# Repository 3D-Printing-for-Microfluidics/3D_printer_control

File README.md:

# 3D Printer Control System

A sophisticated control system for custom DLP-SLA 3D printers, built with Flask and WebSocket communication. This system provides a robust web interface for controlling and monitoring 3D printing operations, with support for various hardware configurations and real-time feedback.

# Overview

This system is designed to control custom DLP-SLA 3D printers using a JSON-based print file format. The print files are validated using a custom JSON schema validator to ensure proper formatting and compatibility. The system supports multiple printer configurations and can be adapted to different hardware setups through its modular architecture.

## System Architecture

### Backend
- Built on Flask web server with modular blueprint structure
- Uses Socket.IO for real-time bidirectional communication between frontend and backend
- Implements a modular hardware driver system for various printer components
- Database-driven job queue management using SQLAlchemy
- Comprehensive logging system with configurable levels and file rotation
- Error handling and recovery mechanisms for hardware failures

### Frontend
- JINJA2 templating engine for HTML structure
- Bootstrap (Darkly theme) for responsive styling
- JavaScript libraries:
  - Socket.IO for real-time communication
  - AJAX for asynchronous requests
  - jQuery for DOM manipulation
  - Popper.js for tooltips and popovers
- Dynamic UI updates for real-time printer status
- Responsive design for various screen sizes

## Hardware Configuration

The system uses a flexible hardware configuration system that:
- Loads hardware configurations based on device hostname
- Supports multiple types of hardware drivers:
  - Virtual hardware (screen, coord_systems, external_control)
  - Abstract base classes and generic drivers (e.g., Visitech light engine, ACS XY/BP stage, Hexapod TTR/focus stage)
  - Regular hardware drivers
- Includes firmware management capabilities through `flash_firmware.sh` RPi script
- Provides dummy drivers for testing and development
- Supports hardware-specific calibration and configuration
- Implements hardware abstraction layers for consistent control interfaces

### Hardware Types
1. **Motion Control**
   - XY stages (ACS, custom implementations)
   - Z-axis control
   - Build plate control
   - Tip-tilt-rotate (TTR) stages
   - Focus stages

2. **Light Control**
   - DLP light engines
   - Screen control systems

3. **Sensors**
   - Load cells
   - Keyence sensors
   - Environmental sensors
   - Accelerometers
   - Light measurement systems

4. **Auxiliary Systems**
   - Vacuum control
   - GPIO control
   - Film control
   - Environmental monitoring

## Core Components

### Manual Controls
- Each hardware driver has associated frontend controls
- Automatically populated based on hardware configuration
- Provides fine-grained control over hardware components
- Allows modification of system settings
- Real-time feedback and status updates
- Safety interlocks and emergency stop functionality

### Views
1. **Print History**
   - Displays recent prints with detailed information
   - Enables job download and re-queue functionality
   - Print success/failure statistics
   - Job parameter history

2. **Server Logs**
   - Shows last 2 weeks of logs
   - Includes calibration position logs
   - Hardware-specific diagnostic information
   - Error tracking and debugging tools

3. **Calibration**
   - Manages printer calibration settings
   - Supports focus, tip, tilt adjustments
   - Integrates with Keyence sensors and Hexapod systems
   - Calibration profile management
   - Automated calibration routines

### Main Printer Control (home.py)
The central control system that:
- Manages print uploads and job queue
- Handles printer planarization
- Controls print operations (start/pause/resume/stop)
- Provides real-time feedback (loadcell data, log messages)
- Implements a dynamic class hierarchy for hardware control
- Error handling and recovery
- State management and synchronization

## Hardware Control Architecture

The system uses a dynamic class composition approach:
- Base `print_control` class defines core functionality
- Hardware-specific subclasses extend functionality
- Class composition is determined by hardware configuration
- Import order is critical for proper initialization and print operations
- Thread-safe operation handling
- Event-driven architecture for hardware interactions

# Raspberry Pi Deployment

This section details the setup process for deploying the system on a Raspberry Pi 5 with NVME storage. See also the `How to do a full install of a HR5 Raspberry Pi` ProjectWiki page for a more detailed guide with rationale.

### Hardware Requirements

- Raspberry Pi 5
- Pimoroni NVME base
- Crucial P3 Plus 1TB SSD (or compatible)
- External SSD housing (for initial setup)

### Initial Setup

1. **Physical Setup**
   - Install NVME SSD and Pimoroni NVME base
   - Follow [Pimoroni NVME base tutorial](https://learn.pimoroni.com/article/getting-started-with-nvme-base)

2. **OS Installation**
   - Download Raspberry Pi Imager
   - Flash Raspberry Pi OS (64-bit) 2024-03-15
   - Configure initial settings:
     - Set hostname (e.g., HR5, MR1v1, HR3v3)
     - Username: pi
     - Password: 3dprinter
     - Timezone: Denver
     - Enable SSH

3. **System Configuration**
   - Configure SSD boot:
     ```bash
     # Edit /boot/firmware/config.txt
     dtparam=pciex1
     nvme_core.default_ps_max_latency_us=0 pcie_aspm=off
     
     # Configure EEPROM
     sudo rpi-eeprom-config --edit
     # Set:
     BOOT_ORDER=0xf416
     PCIE_PROBE=1
     ```
   - Set system clock: `date -s 'YYYY-MM-DD HH:MM:SS'`
   - Configure network:
     - Connect to BYU-Wifi via https://onboard.byu.edu/guest/public/index.html
     - Set static ethernet address (192.168.0.1/24) using `sudo nmtui`
   - Switch to legacy X11:
     ```bash
     sudo raspi-config
     # Advanced Options -> Wayland -> X11
     ```
   - Disable screen blanking:
     ```bash
     sudo raspi-config
     # Display Options -> Screen Blanking -> No
     ```

4. **USB Device Configuration**
   - Create udev rules for USB devices:
     ```bash
     # Wintech
     sudo nano /etc/udev/rules.d/99-wintech.rules
     SUBSYSTEM=="usb",ATTRS{idVendor}=="0451",ATTRS{idProduct}=="c900",GROUP="users",MODE:="0666"
     
     # MKS Controller
     sudo nano /etc/udev/rules.d/99-mks.rules
     SUBSYSTEM=="usb",ATTRS{idVendor}=="0403",ATTRS{idProduct}=="6001",GROUP="users",MODE:="0666"
     
     # Thorlabs Power Meter
     sudo nano /etc/udev/rules.d/99-thorlabspm100.rules
     SUBSYSTEM=="usb",ATTRS{idVendor}=="1313",ATTRS{idProduct}=="8072",GROUP="users",MODE:="0666"
     ```
   - Reload udev rules: `sudo udevadm control --reload-rules`

5. **System Logging**
   - Configure journald:
     ```bash
     # Edit /etc/systemd/journald.conf
     [Journal]
     MaxRetentionSec=1week
     MaxFileSec=1day
     
     # Create journal directory
     mkdir /var/log/journal
     sudo systemd-tmpfiles --create --prefix /var/log/journal
     ```

### Software Installation

1. **Clone Repositories**
   ```bash
   git clone https://github.com/3D-Printing-for-Microfluidics/IP_address_service.git
   git clone https://github.com/gregnordin/3D_printer_control.git
   ```

2. **Install IP Address Service**
   ```bash
   cd IP_address_service/ip_address_service
   sudo -s source ip_address_service_setup.sh
   ```

3. **Setup Python Environment**
   ```bash
   cd 3D_printer_control
   python -m venv env
   source env/bin/activate
   mkdir logs
   
   # Upgrade pip and setuptools
   pip install pip --upgrade
   pip install setuptools --upgrade
   ```

4. **Install Galil Driver**
   ```bash
   # Install CGLib Software
   sudo apt install ./requirements/galil-release_1_all.deb
   sudo apt update
   sudo apt install gclib gcapsd
   ```

5. **Install Python Dependencies**
   ```bash
   pip install -r requirements/prod.txt  # For production
   # or
   pip install -r requirements/dev.txt   # For development
   ```

   Key dependencies include:
   - Flask 3.0.3 with Flask-SocketIO 5.3.6 for web server and real-time communication
   - SQLAlchemy 2.0.31 and Flask-SQLAlchemy 3.1.1 for database management
   - Hardware control libraries:
     - gclib for Galil motion controllers
     - gpiod 2.2.0 and gpiozero 2.0.1 for GPIO control
     - pyserial 3.5 for serial communication
     - pyusb 1.2.1 for USB device control
   - Scientific computing:
     - numpy 2.0.0 and scipy 1.14.1 for numerical operations
     - matplotlib 3.10.1 for plotting
     - pandas 2.2.3 for data manipulation
   - Hardware-specific:
     - ThorlabsPM100 1.2.2 for power meter control
     - seabreeze 2.9.2 for spectrometer integration
     - PIPython 2.10.2.1 for PI motion controllers
   - System utilities:
     - psutil 6.0.0 for system monitoring
     - zeroconf 0.132.2 for network discovery
   - Development tools:
     - jsonschema 4.22.0 for JSON validation
     - scapy 2.5.0 for network analysis

6. **Setup Flask Database**
   ```bash
   source rpi/flask_db_setup.sh
   ```

7. **Configure Systemd Service**
   ```bash
   # Allow X server access
   export DISPLAY=:0.0
   xhost si:localuser:pi
   
   # Create service file
   sudo nano /etc/systemd/system/3d-printer-server.service
   ```
   Add to service file:
   ```ini
   [Unit]
   Description=3D Printer Server
   After=network.target
   
   [Service]
   Type=simple
   WorkingDirectory=/home/pi/3D_printer_control
   Environment=FLASK_APP=/home/pi/3D_printer_control/autoapp.py
   Environment=XAUTHORITY=/home/pi/.Xauthority
   Environment=DISPLAY=:0.0
   ExecStart=/home/pi/3D_printer_control/env/bin/python /home/pi/3D_printer_control/autoapp.py
   Restart=always
   
   [Install]
   WantedBy=multi-user.target
   ```
   Enable and start service:
   ```bash
   sudo systemctl daemon-reload
   sudo systemctl enable 3d-printer-server.service
   sudo systemctl start 3d-printer-server.service
   ```

### Display Configuration

1. **Setup Custom Resolutions**
   ```bash
   # Create autostart directory
   mkdir -p ~/.config/autostart
   
   # Create desktop entry
   nano ~/.config/autostart/xrandr.desktop
   ```
   Add to desktop entry:
   ```ini
   [Desktop Entry]
   Type=Application
   Exec=/home/pi/.config/autostart/xrandr.sh
   Hidden=false
   NoDisplay=false
   X-GNOME-Autostart-enabled=true
   Name[en_US]=Xrandr
   Name=Xrandr
   Comment[en_US]=Set custom resolution using xrandr
   Comment=Set custom resolution using xrandr
   ```
   
   Create resolution script:
   ```bash
   nano ~/.config/autostart/xrandr.sh
   ```
   Add to script:
   ```bash
   #!/bin/sh
   export DISPLAY=:0.0
   
   # Visitech resolution (2560x1600)
   xrandr --newmode "2560x1600_30" 132.68 2560 2608 2640 2720 1600 1603 1609 1623 +hsync -vsync
   xrandr --addmode HDMI-1 2560x1600_30
   xrandr --output HDMI-1 --mode 2560x1600_30
   
   # Wintech resolution (1920x1080)
   xrandr --newmode "1920x1080_60" 148.50 1920 2008 2096 2200 1080 1084 1089 1125 +hsync -vsync
   xrandr --addmode HDMI-2 1920x1080_60
   xrandr --output HDMI-2 --mode 1920x1080_60
   ```
   Make script executable:
   ```bash
   chmod +x ~/.config/autostart/xrandr.sh
   ```

### Additional Hardware Notes

- Spectrometer: Update firmware to NI-VISA version using Thorlabs Driver Switcher
- PI Hexapod stage: Update IP address to match subnet (192.168.x.x)
- ACS stages: Configure static IP and update to match subnet

# Development Setup

### Prerequisites
- Python 3.5 or higher
- Virtual environment (recommended)
- Required Python packages (see requirements/dev.txt)
- Git

### Installation Steps
1. Clone the repository
2. Create and activate virtual environment:
   ```bash
   python -m virtualenv env
   source env/bin/activate  # On Windows: env\Scripts\activate
   ```
3. Install dependencies:
   ```bash
   pip install -r requirements/dev.txt
   ```
4. Set up environment variables:
   ```bash
   export FLASK_APP=tests/dummy_server.py
   export FLASK_DEBUG=1  # For development mode
   ```
5. Initialize database:
   ```bash
   flask db init
   flask db migrate
   flask db upgrade
   ```

### Running the Development Server
1. Start the server:
   ```bash
   python $FLASK_APP
   ```
2. Access the web interface at `http://127.0.0.1:5000`
3. For external access, modify `app.py` to use `0.0.0.0:port`

### Development Tips
- Use Incognito mode to prevent browser caching
- Press `Ctrl+F5` in Chrome to force refresh
- Monitor terminal output for debug information
- Check logs in `printer_server/logs/`

# Active Branches

This repository maintains several branches for different printer configurations:
- `master` - Stable branch for 3D printers
- `dev/ branches` - Current active development branches
- `feature/ branches` - Branches adding new feature to 3D printers
- `stable/ branches` - Legacy release branches no longer in use
- `gen1-1` - Legacy software for HR1.1 3D printer

# Troubleshooting

### Common Issues

1. **Hardware Connection**
   - Check USB connections
   - Verify permissions
   - Test hardware directly
   - Check logs for errors

2. **Firmware Issues**
   - Verify firmware version
   - Check flash process
   - Review error logs
   - Test with dummy firmware

3. **Web Interface**
   - Clear browser cache
   - Check Socket.IO connection
   - Verify JavaScript console
   - Test in incognito mode

# Additional Resources

- [Flask Documentation](http://flask.pocoo.org/docs/1.0/quickstart/)
- [Python Virtual Environment Guide](https://docs.python.org/3/tutorial/venv.html)
- [Socket.IO Documentation](https://socket.io/docs/)
- [Bootstrap Documentation](https://getbootstrap.com/docs/)

# License

This project is licensed under the terms specified in the LICENSE.txt file.

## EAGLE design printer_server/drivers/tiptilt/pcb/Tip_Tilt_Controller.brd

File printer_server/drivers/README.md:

# 3D Printer Hardware Drivers

This directory contains the hardware drivers for controlling various components of the 3D printer system. The drivers are designed with a modular architecture that supports both real hardware and dummy implementations for testing.

## Driver Architecture

The driver system follows a hierarchical design with:
- Abstract base classes in `generic_drivers/` defining common interfaces
- Concrete implementations for specific hardware
- Dummy implementations for testing and development

### Base Classes

The `generic_drivers/` directory contains abstract base classes for different types of hardware:

1. **Stage Drivers**
   - `BPStageDriver`: Build platform stage control
   - `XYStageDriver`: XY motion stage control
   - `FocusStageDriver`: Focus stage control
   - `TTRStageDriver`: Tip-tilt-rotate stage control

2. **Communication Drivers**
   - `EthernetSerial`: Base class for Ethernet-based serial communication
   - `USBSerial`: Base class USB-based serial communication

## Available Drivers

### Motion Control
- `acs/`: ACS motion controller driver
- `galil/`: Galil motion controller driver
- `hexapod/`: Hexapod stage driver
- `thorlabs_apt`: Thorlabs motor driver for KDC101 and LTS stages
- `tiptilt/`: Custom Tip-tilt stage driver for optical alignment

### Light Control
- `screen/`: Screen control system
- `visitech/`: Visitech light engine driver
- `wintech/`: Wintech DLP controller driver

### Sensors
- `accelerometer/`: Accelerometer driver
- `environmental_sensors/`: Environmental monitoring sensors
- `keyence/`: Keyence confocal displacement sensor driver
- `loadcell/`: Load cell sensor for force measurement
- `photodiode/`: Photodiode sensor driver
- `spectrometer/`: Spectrometer driver

### Auxillary Control
- `external_control/`: External control system interface
- `gpio/`: General Purpose I/O control
- `mks/`: MKS 946 pressure controller driver
- `mks_teensy/`: Teensy-based MKS controller and GPIO interface

### Other
- `coord_systems/`: Coordinate system transformation utilities

## Driver Implementation

Each driver follows a common pattern:
1. Inherits from appropriate base class
2. Implements required interface methods
3. Provides hardware-specific functionality
4. Includes error handling and logging
5. Supports both real and dummy implementations

### Example Usage

```python
from printer_server.drivers.galil import Galil, Galil_dummy

# For real hardware
driver = Galil(config_dict=config, log_level=logging.INFO)

# For testing/development
driver = Galil_dummy(config_dict=config, log_level=logging.INFO)
```

## Adding New Drivers

To add a new driver:

1. Create a new directory in `drivers/`
2. Implement the driver class inheriting from appropriate base class
3. Create a dummy implementation for testing
4. Add driver configuration to hardware configuration JSON
5. Update `hardware_configuration.py` to support the new driver

## Testing

Each driver should have:
- A dummy implementation for testing
- Appropriate Manual Control _snip code

## Configuration

Drivers are configured through JSON files in the `hardware_configuration/` directory. Each driver can specify:
- Connection parameters
- Hardware-specific settings
- Dummy mode for testing
- Logging configuration

## Error Handling

Drivers implement comprehensive error handling:
- Connection failures
- Hardware communication errors
- Invalid commands
- Timeout handling
- Recovery procedures

## Logging

All drivers use the Python logging system with:
- Configurable log levels
- Hardware-specific log messages
- Error tracking
- Performance monitoring

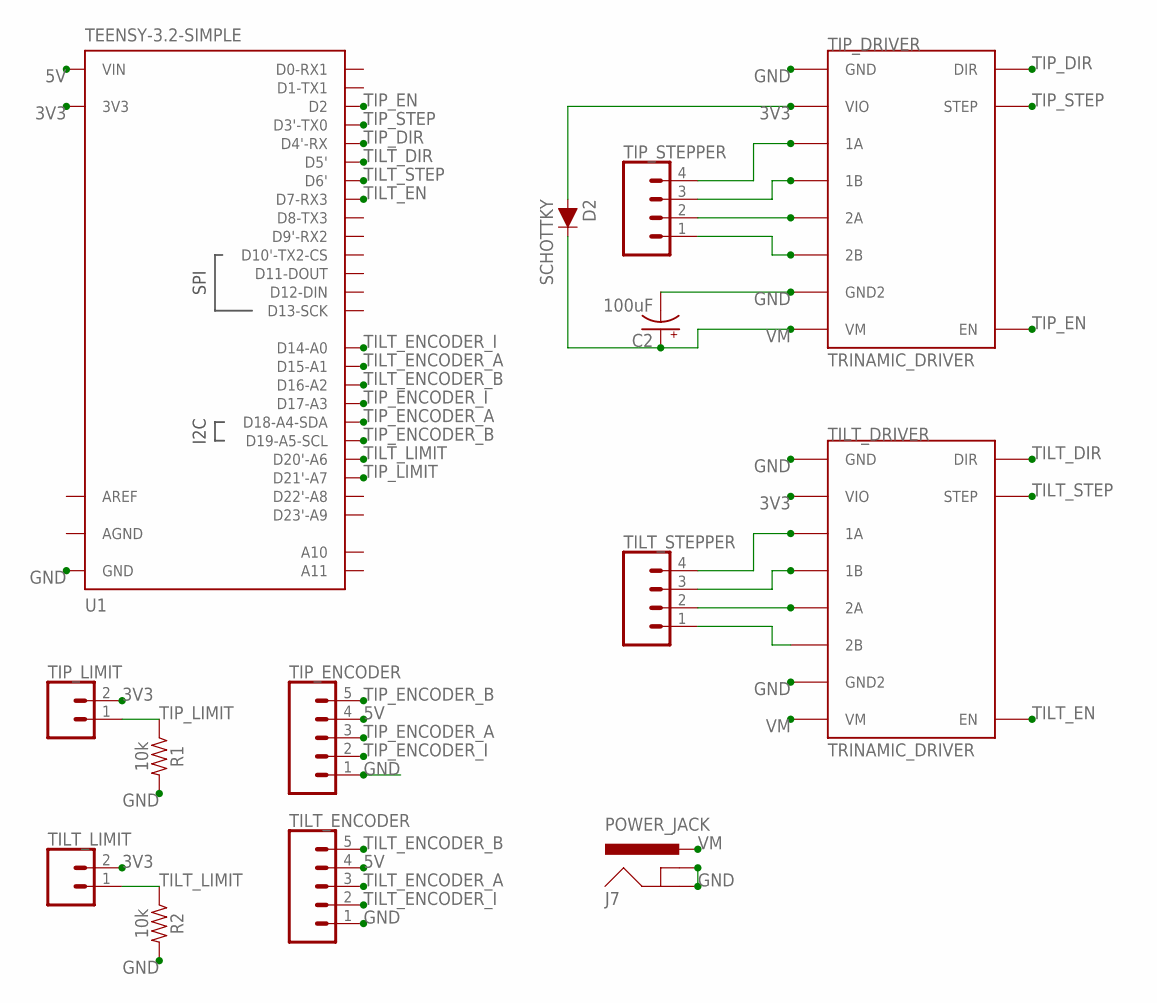
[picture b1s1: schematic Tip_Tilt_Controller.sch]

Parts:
C2: 100uF; CPOL-RADIAL-2.5MM-6.5MM
D2: SCHOTTKY; DIODE-1N4148
J7: POWER_JACK; POWER_JACK_PTH
R1, R2: 10k; AXIAL-0.3
TILT_DRIVER: TRINAMIC_DRIVER
TILT_ENCODER: CONN_05; 1X05
TILT_LIMIT: CONN_02; 1X02
TILT_STEPPER: CONN_04PTH; 1X04
TIP_DRIVER: TRINAMIC_DRIVER
TIP_ENCODER: CONN_05; 1X05
TIP_LIMIT: CONN_02; 1X02
TIP_STEPPER: CONN_04PTH; 1X04
U1: TEENSY-3.2-SIMPLE

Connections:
3V3: D2.A, TILT_DRIVER.5V (VIO), TILT_LIMIT.2, TIP_DRIVER.5V (VIO), TIP_LIMIT.2, U1.3.3V (3V3)
5V: TILT_ENCODER.4, TIP_ENCODER.4, U1.VIN
AGND: U1.AGND
AREF: U1.AREF
GND: C2.2 (-), J7.GND, J7.GNDBREAK, R1.P$2 (2), R2.P$2 (2), TILT_DRIVER.GND, TILT_DRIVER.GND2, TILT_ENCODER.1, TIP_DRIVER.GND, TIP_DRIVER.GND2, TIP_ENCODER.1, U1.GND
unnamed: TIP_DRIVER.1A, TIP_STEPPER.4
unnamed: TIP_DRIVER.1B, TIP_STEPPER.3
unnamed: TIP_DRIVER.2A, TIP_STEPPER.2
unnamed: TIP_DRIVER.2B, TIP_STEPPER.1
unnamed: TILT_DRIVER.1A, TILT_STEPPER.4
unnamed: TILT_DRIVER.1B, TILT_STEPPER.3
unnamed: TILT_DRIVER.2A, TILT_STEPPER.2
unnamed: TILT_DRIVER.2B, TILT_STEPPER.1
TILT_DIR: TILT_DRIVER.DIR, U1.5 (D5')
TILT_EN: TILT_DRIVER.EN, U1.7 (D7-RX3)
TILT_ENCODER_A: TILT_ENCODER.3, U1.15 (D15-A1)
TILT_ENCODER_B: TILT_ENCODER.5, U1.16 (D16-A2)
TILT_ENCODER_I: TILT_ENCODER.2, U1.14 (D14-A0)
TILT_LIMIT: R2.P$1 (1), TILT_LIMIT.1, U1.20 (D20'-A6)
TILT_STEP: TILT_DRIVER.STEP, U1.6 (D6')
TIP_DIR: TIP_DRIVER.DIR, U1.4 (D4'-RX)
TIP_EN: TIP_DRIVER.EN, U1.2 (D2)
TIP_ENCODER_A: TIP_ENCODER.3, U1.18 (D18-A4-SDA)
TIP_ENCODER_B: TIP_ENCODER.5, U1.19 (D19-A5-SCL)
TIP_ENCODER_I: TIP_ENCODER.2, U1.17 (D17-A3)
TIP_LIMIT: R1.P$1 (1), TIP_LIMIT.1, U1.21 (D21'-A7)
TIP_STEP: TIP_DRIVER.STEP, U1.3 (D3'-TX0)
VM: C2.1 (+), D2.C, J7.PWR, TILT_DRIVER.VM, TIP_DRIVER.VM

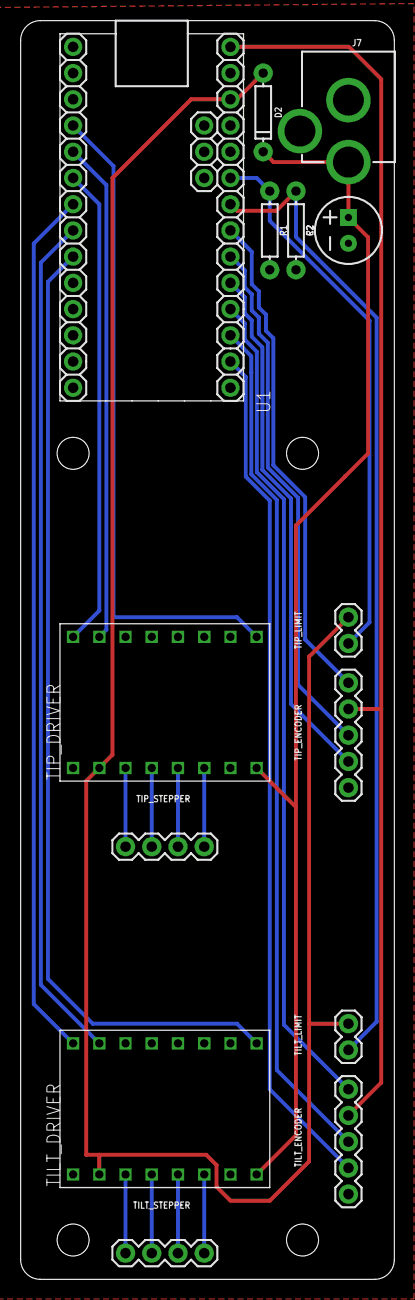
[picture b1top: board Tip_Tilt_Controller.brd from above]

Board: 2 copper layers, 36.2 x 121.9 mm, 14 parts (0 on the bottom side), 26 nets.

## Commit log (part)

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2024-12-31 Prevent loop racing in TT
2024-12-31 Actually call TTR logging start/stop
2024-12-31 Fix other race events
2024-12-31 speed up keyence measurements
2024-12-31 Remove extra wait in light engine driver exposures
2024-12-31 Increase resolution and update rate of loadcell plot
2024-12-31 Fix bug in GPIO film mc
2024-12-31 Rename tt log
2025-01-02 Fixed Tiptilt driver float rounding
2025-01-02 Change last commit to increse precision
2025-01-02 One more...
2025-01-02 Fix cast error in KDC
2025-01-03 Fix ttr bug in calibration
2025-01-03 Fix trig error in MirrorTipTilt
2025-01-03 Add undef if tt not initialized. Speed up movements
2025-01-03 Add nm label to le source
2025-01-09 Add microcode libraries, firmware scripts, and firmware binaries
2025-01-09 Split mks and mks_teensy, also a few bug fixes
2025-01-09 Fix bug introduced in f4f2584
2025-01-31 Reduce loadcell drawing
2025-01-31 Hopefully fix TT loop failing
2025-01-31 Reduce loadcell planarization to 35N
2025-01-31 Update HR5 settings (note grayscale corr is included...)
2025-01-31 Add grayscale corrections
2025-01-31 Add TestControl
2025-01-31 Update light_measurement_control
2025-01-31 Add second finish plan for HR5
2025-02-24 Add more delay to degas vent
2025-02-24 First pass at test code for hannah and heidi
2025-02-24 Fix bug in last
2025-02-24 Add multiple scan lines to test
2025-03-07 Add vaccum control for prints (still need to do some kind of json enabling)
2025-03-07 Add logging to last commit
2025-03-07 Adjusting vacuum targets
2025-03-07 Add extra check ot bell jar venting
2025-03-07 Move MKSControl before LoadcellControl
2025-03-07 Fix critical bug
2025-03-07 Fix bug in vaccum control
2025-03-10 Add "Print under vacuum" to json and add planarization vacuum logging
2025-03-10 Cleanup loadcell set_log_file
2025-03-10 Only do planarization a 2nd time if "Print under vacuum"
2025-03-10 Fix bug in new vaccum code
2025-03-10 Another fix to vacuum code
2025-03-13 Add Y-offset to keyence line test
2025-03-17 Hopefully fix accelerometer freezing
2025-03-19 Fix issue with vacuum valve priorities
2025-03-21 Still trying to fix hanging at end of print
2025-03-25 Worked on grayscale scan and analysis test code
2025-03-25 Speed up print and add correction
2025-03-25 Fix bug in last commit
2025-03-28 Change fast photodiode position
2025-03-28 Tweek last commit
2025-04-09 Add film membrane to json and validator
2025-04-09 Recompress cleaned uploaded file
2025-04-11 Update requirements again
2025-04-11 Updated installation README and files to save galil/gclib install files
2025-04-11 Updated reqirements to include gclib
2025-04-14 Add normaization factor of 1 to 3v3u json
2025-04-14 Fix bug in normalization base case
2025-04-15 Fix bug in MR1v1 calibration
2025-04-19 Add thermal drift calculations for MR1v1
2025-04-19 Fix bugs in new keyence thermal code
2025-04-19 Fix bug in grayscale on visitech
2025-04-19 Fix another bug in the thermal code
2025-04-19 Tweek progress bar
2025-04-19 Add debug statements to new keyence measurements
2025-04-19 Trying to figure out what is not working
2025-04-20 Switch temporary print statements to event log
2025-04-21 Clean up code, add origin thermal measure, and fix crash
2025-04-21 Correct for backlash in griffin focus & add thermal expantion log
2025-04-21 Fix bug in thermal logging
2025-04-21 Another bug
2025-04-21 Remove keyence focus stage jiggle
2025-04-21 Final cleanup
2025-04-22 Remove temp logging, move all keyence logs to log file, swap origin measurement to only failed cont measurements
2025-04-22 Fix bug
2025-04-22 Update again
2025-04-22 Again
2025-04-23 Fix typo
2025-05-09 Add wintech fan control
2025-05-09 More bug fix
2025-05-09 Set fans to be default on
2025-05-09 Swap fan polarity
2025-05-09 Undo last
2025-05-09 Final fan commit
2025-07-28 Fix bug in dev.txt
2025-07-28 Update 3v3u loadcell settings
2025-07-29 update to galil controller
2025-07-30 Update KDC and os1 hardware config
2025-07-30 Fixed os1v0 hw-conf and renamed kdc101
2025-07-30 Fix os1 loadcell pid
2025-07-30 Fix hw-conf
2025-07-30 Fix multi-inheritance of thorlabs-apt driver
2025-07-31 Fix apt limits bug
2025-07-31 Add delay after apt home
2025-07-31 Update ttrf limits to use rad
2025-07-31 Update os1 coords, speeds, limits, and homing speeds
2025-07-31 Update 3 series to use kdc101_ttrf
2025-08-01 Fix apt connect
2025-08-01 Fix apt limit issues
2025-08-01 Update apt homing speeds
2025-08-01 Tweek log messages
2025-08-01 Cleanup apt
2025-08-01 Fix limits
2025-08-01 Fix bug in ttrf limits
2025-08-01 Update bp, xy, focus limits to update on mc
2025-08-01 Double tip/tilt angles
2025-08-05 updated serial number
2025-08-05 planarization motor initialization bugfixes
2025-08-05 planarization motor initialization bug fixes
2025-08-05 bug fixes
2025-08-05 updated planarization firmware
2025-08-05 firmware flashing bug fixed?
2025-08-05 turned on dummy drivers for testing
2025-08-05 firmware flashing name reconcilliation
2025-08-06 small bug squash
2025-08-06 Update OS1 hwconf
2025-08-06 Fix bugs in motor planarization
2025-08-06 fixed pointer issue
2025-08-06 Fix bug in planarization threading
2025-08-07 Mostly finish motorized planarization
2025-08-07 added supported versions
2025-08-07 Fix bug in ttr join
2025-08-07 Fix bug in clickable row
2025-08-08 Add first pass at keyence tip/tilt
2025-08-12 separation of photodiode and spectrometer in light measurement control
2025-08-12 Add in Visitech initialization check
2025-08-12 manual controls for planarization motor
2025-08-12 intuitive change so that loosen sets target torque to 0.0
2025-09-05 Add orientation to config json
2025-09-05 Update OS1 coords
2025-09-05 Adjust OS1 speeds and accelerations
2025-09-05 Adjust OS1 planarization settings
2025-09-05 Try to fix rare screen drawing failure
2025-09-05 Tweek kdc101ttrf tip multiplier
2025-09-05 Adjust visitech DMD operation to wait until video lock
2025-09-05 Force visitech to validate video lock on init
2025-09-05 Add 999 schema to OS1
2025-09-05 Swap auto_tip_tilt to test control
2025-09-05 Overhaul test control (progress, le alignment, stage linking, new photodiode centering process, grayscale json updating, keyence/photodiode tip/tilt) BROKEN HR5 MIRRORING
2025-09-05 Fix bugs in and tweek planarization
2025-09-18 Fix bug in MR1 Visitech focus
2025-10-15 Add variables to print schema
2025-10-15 Add simpleeval req
2025-10-15 Fix last
2025-10-16 Update HR5 coords, vacuum levels, and grayscale correction code
2025-10-16 Add logging to screen image not found
2025-10-16 Add calibration images to visitech
2025-10-16 Remove print statement
2025-10-16 Add grayscale correction image to OS1 hwconf
2025-10-16 Rename keyence control
2025-10-16 Update test_control plotting and use builtin calibration images
2025-10-16 Update gitignore
2025-11-19 Update MR1v1 coords
2025-11-19 Update json validator with membrane on film change
2026-01-29 debugging on printer pi
2026-02-09 Updated to json v5
2026-02-09 Fix schema bug
2026-02-09 Take 2
2026-02-09 Take 3
2026-02-09 Ok. For reals this time??
2026-02-10 Fix bug in squeeze force and add debug print for testing
2026-02-10 Remove debug prints
2026-02-10 Fixed last
2026-02-10 Fix printer_compatibiliy vaccum check
2026-02-10 Add wait time to "print on film" technique
2026-02-10 Increase max print history length from 500 to 2500
2026-02-16 Fix some broken code on OS1 branch
2026-02-16 Update 3 series ttrf to match os1
2026-02-16 Implement calibration prints
2026-02-16 Removed info and fixed variables to be pythonic
2026-02-16 Try alternate rendering for prints
2026-02-16 Adjusted print file names and layout. (also renamed calibration print)
2026-02-17 Add debug prints
2026-02-17 Fix translation dict
2026-02-17 First test of active irradiance correction
2026-02-17 Add debug print
2026-02-17 Fixed bugs
2026-02-17 Rearranged calibration parameters
2026-02-17 Try to get group headers
2026-02-17 Tweek irradinace names
2026-02-17 Try to fix broken buttons
2026-02-18 Add sweep and uniform focus prints
2026-02-18 Limit calibration prints and add header
2026-02-18 Adjust print file name display
2026-02-18 Increase header size
2026-02-18 Fix bug in new active irradance correction
2026-02-18 Update OS1 hw config
2026-02-19 Fix bug with visitechs not init-ing
2026-02-20 Update calibration print files
2026-02-20 Added timeout to loadcell planarization
2026-02-20 Fix bug in defocus
2026-02-20 Change permissions of reset HDMI
2026-03-04 A few tweeks to focus stage linking
2026-03-04 Add Tip/Tilt focus print
2026-03-04 Add calibration prints to os1
2026-03-04 Update tt focus cal print readme
2026-03-04 Update print again
2026-03-04 Update cal readmes and add grayscale correction cal
2026-03-04 Add grayscale cal print to os1
2026-03-09 Update HR5 grayscale calibration
2026-03-23 Changed calibration prints to load from zip
2026-03-23 Remove non-zipped calibration prints
2026-03-23 Fix bug in galil stage homing
2026-03-23 Fix bug in loadcell planarization
2026-03-23 Update calibration print
2026-03-25 Added search, filter, and sort to print history
2026-03-31 Fix issues in backfill script
2026-03-31 Update calibration prints
2026-03-31 Add image mirroring to JSON
2026-03-31 Add image mirroring to hwconfig
2026-03-31 Add design header to v999 schema
2026-03-31 Fix print history column selector layout
2026-03-31 Fixed bugs in stage limits (couldn't disable)
2026-03-31 Moved auto_focus parameters to respective hardware
2026-03-31 Add parameter for keyence direct_focal_measurement and thermal_drift_measurement
2026-03-31 Reorganized calibration page
2026-03-31 Cleanup test_control and fix some broken tests
2026-03-31 Standarize motion command on threaded movement
2026-03-31 Round all motion stages to 4 digits of precision
2026-03-31 Fix bugs in 3 series hwconfig
2026-03-31 Get grayscale correction mapping working with new mirroring
2026-03-31 Fix image stitching
2026-03-31 Cleanup code
2026-04-09 Add prev_position setter in jogging
2026-04-09 Remove bp from coordinate system
2026-04-09 Fix bug in extract calibration order
2026-04-09 Move all moves to threaded functions, add xyf move function, and fix keyence focus
2026-04-09 Add OS1 stitching alignment print
2026-04-09 Remove old code
2026-04-09 Fix bug in test control (center tt)
2026-04-14 Update HDMI reset to also reset tkinter virtual screen
2026-04-14 tweek backfill script
2026-05-07 Fix code bug in focus stage linking
2026-05-11 Fix rare bugs where print fails to start
2026-05-14 Suppress wintech warning on MR1 print finish
2026-05-19 Add audio cues
2026-05-19 Update dummy drivers
2026-05-19 Fix bugs in mc loadcell start
2026-05-22 HR3v3u grayscale correction
2026-05-22 Adjust print sounds
2026-05-26 Update HR3v3u TTRF
2026-05-26 Update HR3v3u normalization
2026-05-26 Add HR3v3 and OS1 grayscale/normalization
2026-05-26 Default to normalized
2026-05-26 Update HR3v3 normalization
2026-05-27 Fix bug in grayscale default
2026-05-27 Update 3 series again
2026-05-29 Change sounds
2026-06-01 Update HR3v3 TTRF to new system
2026-06-01 Update auto planarization firmware
2026-06-01 Add auto planarization to HR3v3u
2026-06-04 Change um to μm on mc pages
2026-06-04 Add new grayscale report
2026-06-04 Fix threading bug in xy/focus control
2026-06-05 Update License
2026-06-11 Remove photodiode focus and tip/tilt
2026-06-11 Rename le name conversion function
2026-06-11 Move virtual screen into light engine drivers (missing test_control)
2026-06-11 Update test_control (new screen, grayscale scan transforms, grayscale check only flag, bug fixes in report)
2026-06-11 Fix bug in thorlabs apt mirroring
2026-06-11 Update json readme
2026-06-11 Fix bugs in grayscale default and screen restart
2026-06-11 Update saves prints from 2.5k to 15k
2026-06-12 Fix bug in new grayscale defaults
2026-06-15 Add new models and forms
2026-06-15 Remove unused logging handler
2026-06-17 Add new reqs
2026-06-17 Fix JS bug on home
2026-06-17 Move calibration positions to db & change models to have classmethods
2026-06-17 Fully working sessions
2026-06-23 Lots of work getting tables working
2026-06-23 Fix spelling error
2026-06-29 Add session summary
2026-06-29 Leave all calibrations per session
2026-06-29 Don't log focus_base

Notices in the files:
parts and their libraries:
SparkFun-Capacitors: Licensing: Creative Commons ShareAlike 4.0 International - https://creativecommons.org/licenses/by-sa/4.0
